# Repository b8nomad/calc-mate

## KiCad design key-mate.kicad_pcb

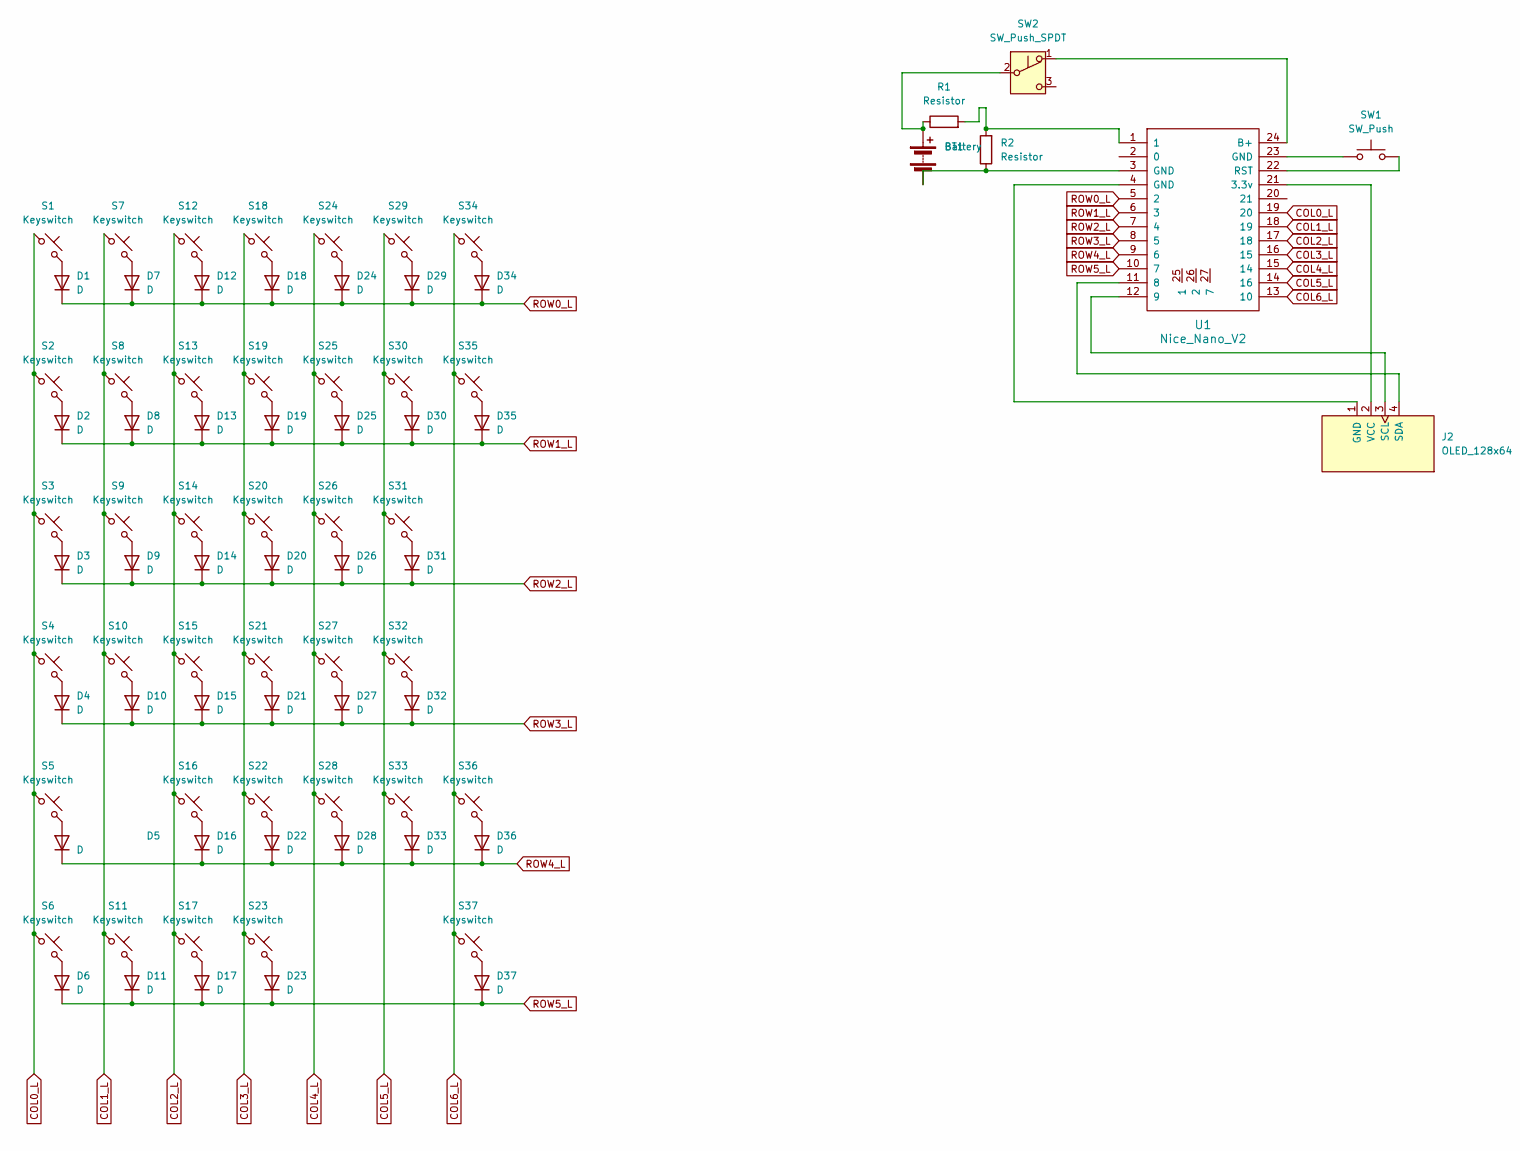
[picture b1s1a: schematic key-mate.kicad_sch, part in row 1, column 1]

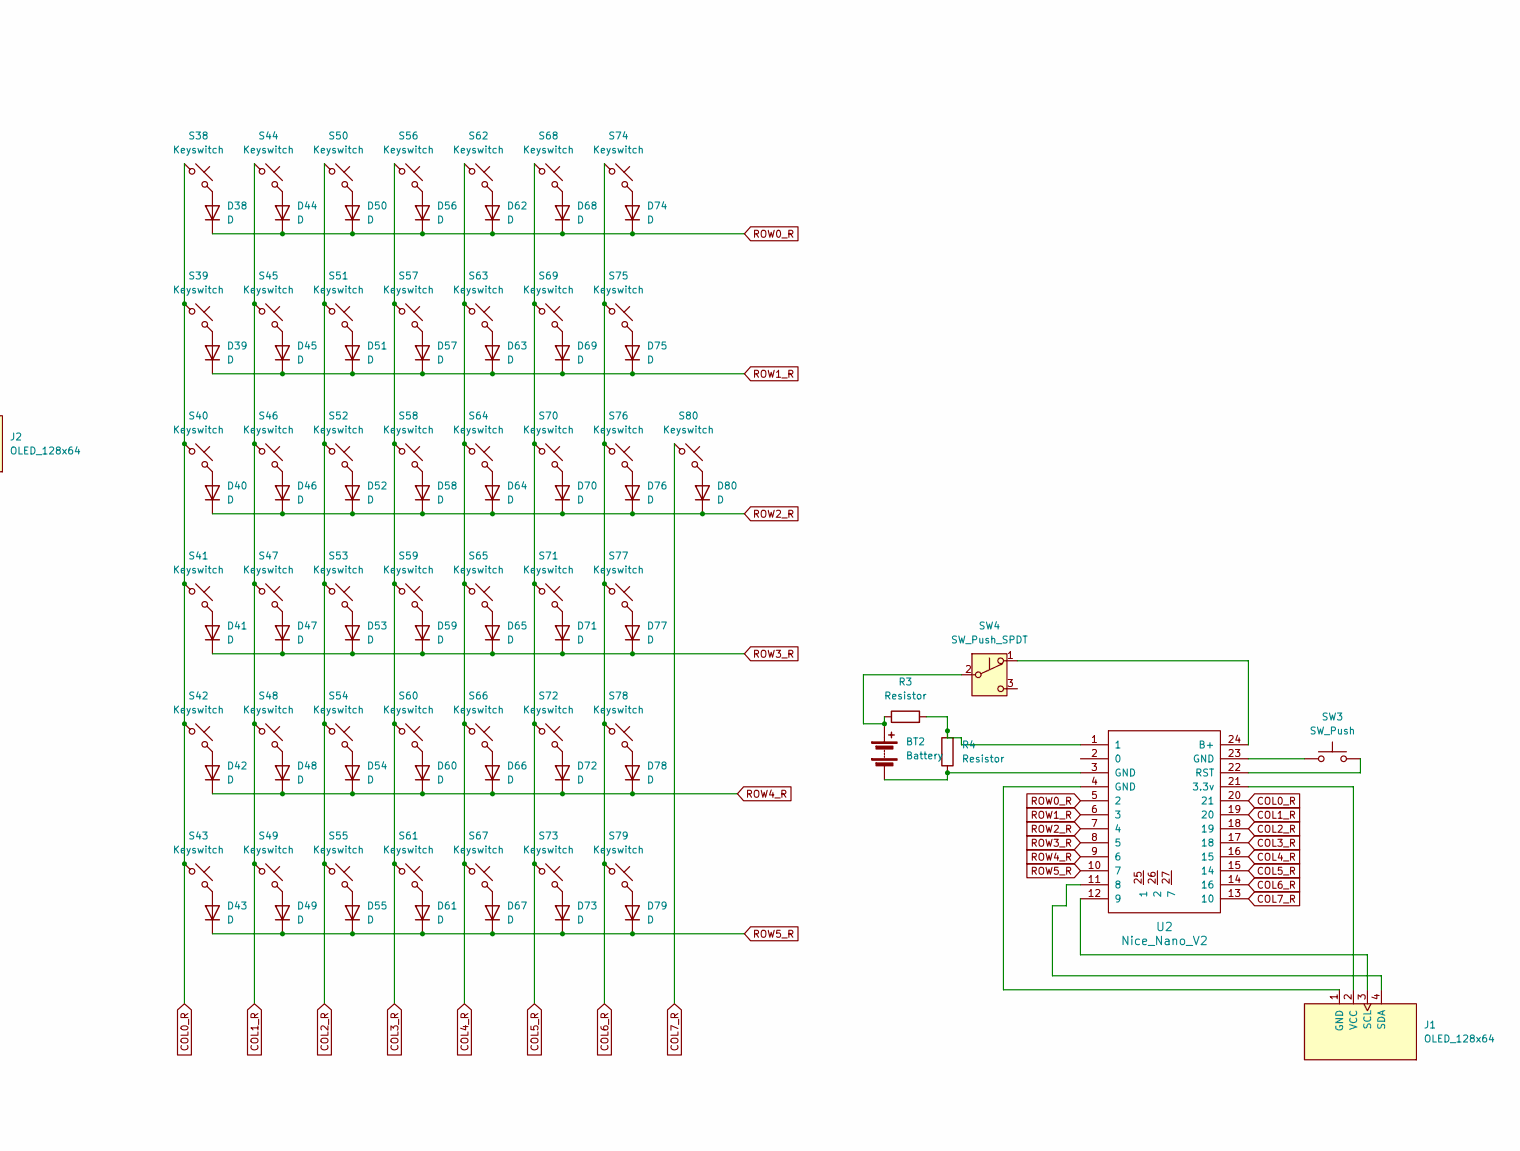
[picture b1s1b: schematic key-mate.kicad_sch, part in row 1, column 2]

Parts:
BT1, BT2: Battery
D1, D2, D3, D4, D5, D6, D7, D8, D9, D10, D11, D12, D13, D14, D15, D16, D17, D18, D19, D20, D21, D22, D23, D24, D25, D26, D27, D28, D29, D30, D31, D32, D33, D34, D35, D36, D37, D38, D39, D40, D41, D42, D43, D44, D45, D46, D47, D48, D49, D50, D51, D52, D53, D54, D55, D56, D57, D58, D59, D60, D61, D62, D63, D64, D65, D66, D67, D68, D69, D70, D71, D72, D73, D74, D75, D76, D77, D78, D79, D80: D; Diode_SOD-123
J1, J2: OLED_128x64
R1, R3: Resistor; Resistor_0402
R2, R4: Resistor; Resistor_0805
S1, S3, S75: Keyswitch; Hotswap_MX_1.50u
S2, S6, S7, S8, S9, S10, S11, S12, S13, S14, S15, S16, S17, S18, S19, S20, S21, S22, S23, S24, S25, S26, S27, S28, S29, S30, S31, S32, S33, S34, S35, S36, S38, S39, S40, S41, S42, S44, S45, S46, S47, S48, S49, S50, S51, S52, S53, S54, S55, S56, S57, S58, S59, S60, S61, S62, S63, S64, S65, S66, S67, S68, S69, S70, S71, S73, S74, S76, S78, S79, S80: Keyswitch; Hotswap_MX_1.00u
S4, S77: Keyswitch; Hotswap_MX_1.75u
S5, S72: Keyswitch; Hotswap_MX_2.25u
S37: Keyswitch; Hotswap_MX_3.00u
S43: Keyswitch; Hotswap_MX_4.00u
SW1, SW3: SW_Push; Button_MJTP1243
SW2, SW4: SW_Push_SPDT; Switch_SSAL220100
U1, U2: Nice_Nano_V2

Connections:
COL0_L: S1.1, S2.1, S3.1, S4.1, S5.1, S6.1, U1.19 (20)
COL0_R: S38.1, S39.1, S40.1, S41.1, S42.1, S43.1, U2.20 (21)
COL1_L: S7.1, S8.1, S9.1, S10.1, S11.1, U1.18 (19)
COL1_R: S44.1, S45.1, S46.1, S47.1, S48.1, S49.1, U2.19 (20)
COL2_L: S12.1, S13.1, S14.1, S15.1, S16.1, S17.1, U1.17 (18)
COL2_R: S50.1, S51.1, S52.1, S53.1, S54.1, S55.1, U2.18 (19)
COL3_L: S18.1, S19.1, S20.1, S21.1, S22.1, S23.1, U1.16 (15)
COL3_R: S56.1, S57.1, S58.1, S59.1, S60.1, S61.1, U2.17 (18)
COL4_L: S24.1, S25.1, S26.1, S27.1, S28.1, U1.15 (14)
COL4_R: S62.1, S63.1, S64.1, S65.1, S66.1, S67.1, U2.16 (15)
COL5_L: S29.1, S30.1, S31.1, S32.1, S33.1, U1.14 (16)
COL5_R: S68.1, S69.1, S70.1, S71.1, S72.1, S73.1, U2.15 (14)
COL6_L: S34.1, S35.1, S36.1, S37.1, U1.13 (10)
COL6_R: S74.1, S75.1, S76.1, S77.1, S78.1, S79.1, U2.14 (16)
COL7_R: S80.1, U2.13 (10)
unnamed: BT1.1 (+), R1.1, SW2.2 (B)
unnamed: BT1.2 (-), R2.1, U1.3 (GND)
unnamed: BT2.1 (+), R3.1, SW4.2 (B)
unnamed: BT2.2 (-), R4.1, U2.3 (GND)
unnamed: D1.2 (A), S1.2
unnamed: D2.2 (A), S2.2
unnamed: D3.2 (A), S3.2
unnamed: D4.2 (A), S4.2
unnamed: D5.2 (A), S5.2
unnamed: D6.2 (A), S6.2
unnamed: D7.2 (A), S7.2
unnamed: D8.2 (A), S8.2
unnamed: D9.2 (A), S9.2
unnamed: D10.2 (A), S10.2
unnamed: D11.2 (A), S11.2
unnamed: D12.2 (A), S12.2
unnamed: D13.2 (A), S13.2
unnamed: D14.2 (A), S14.2
unnamed: D15.2 (A), S15.2
unnamed: D16.2 (A), S16.2
unnamed: D17.2 (A), S17.2
unnamed: D18.2 (A), S18.2
unnamed: D19.2 (A), S19.2
unnamed: D20.2 (A), S20.2
unnamed: D21.2 (A), S21.2
unnamed: D22.2 (A), S22.2
unnamed: D23.2 (A), S23.2
unnamed: D24.2 (A), S24.2
unnamed: D25.2 (A), S25.2
unnamed: D26.2 (A), S26.2
unnamed: D27.2 (A), S27.2
unnamed: D28.2 (A), S28.2
unnamed: D29.2 (A), S29.2
unnamed: D30.2 (A), S30.2
unnamed: D31.2 (A), S31.2
unnamed: D32.2 (A), S32.2
unnamed: D33.2 (A), S33.2
unnamed: D34.2 (A), S34.2
unnamed: D35.2 (A), S35.2
unnamed: D36.2 (A), S36.2
unnamed: D37.2 (A), S37.2
unnamed: D38.2 (A), S38.2
unnamed: D39.2 (A), S39.2
unnamed: D40.2 (A), S40.2
unnamed: D41.2 (A), S41.2
unnamed: D42.2 (A), S42.2
unnamed: D43.2 (A), S43.2
unnamed: D44.2 (A), S44.2
unnamed: D45.2 (A), S45.2
unnamed: D46.2 (A), S46.2
unnamed: D47.2 (A), S47.2
unnamed: D48.2 (A), S48.2
unnamed: D49.2 (A), S49.2
unnamed: D50.2 (A), S50.2
unnamed: D51.2 (A), S51.2
unnamed: D52.2 (A), S52.2
unnamed: D53.2 (A), S53.2
unnamed: D54.2 (A), S54.2
unnamed: D55.2 (A), S55.2
unnamed: D56.2 (A), S56.2
unnamed: D57.2 (A), S57.2
unnamed: D58.2 (A), S58.2
unnamed: D59.2 (A), S59.2
unnamed: D60.2 (A), S60.2
unnamed: D61.2 (A), S61.2
unnamed: D62.2 (A), S62.2
unnamed: D63.2 (A), S63.2
unnamed: D64.2 (A), S64.2
unnamed: D65.2 (A), S65.2
unnamed: D66.2 (A), S66.2
unnamed: D67.2 (A), S67.2
unnamed: D68.2 (A), S68.2
unnamed: D69.2 (A), S69.2
unnamed: D70.2 (A), S70.2
unnamed: D71.2 (A), S71.2
unnamed: D72.2 (A), S72.2
unnamed: D73.2 (A), S73.2
unnamed: D74.2 (A), S74.2
unnamed: D75.2 (A), S75.2
unnamed: D76.2 (A), S76.2
unnamed: D77.2 (A), S77.2
unnamed: D78.2 (A), S78.2
unnamed: D79.2 (A), S79.2
unnamed: D80.2 (A), S80.2
unnamed: J1.1 (GND), U2.4 (GND)
unnamed: J1.3 (SCL), U2.12 (9)
unnamed: J1.4 (SDA), U2.11 (8)
unnamed: J1.2 (VCC), U2.21 (3.3v)
unnamed: J2.1 (GND), U1.4 (GND)
unnamed: J2.3 (SCL), U1.12 (9)
unnamed: J2.4 (SDA), U1.11 (8)
unnamed: J2.2 (VCC), U1.21 (3.3v)
unnamed: R1.2, R2.2, U1.1
unnamed: R3.2, R4.2, U2.1
unnamed: SW1.1, U1.23 (GND)
unnamed: SW2.1 (A), U1.24 (B+)
unnamed: SW3.1, U2.23 (GND)
unnamed: SW4.1 (A), U2.24 (B+)
unnamed: SW1.2, U1.22 (RST)
unnamed: SW3.2, U2.22 (RST)
ROW0_L: D1.1 (K), D7.1 (K), D12.1 (K), D18.1 (K), D24.1 (K), D29.1 (K), D34.1 (K), U1.5 (2)
ROW0_R: D38.1 (K), D44.1 (K), D50.1 (K), D56.1 (K), D62.1 (K), D68.1 (K), D74.1 (K), U2.5 (2)
ROW1_L: D2.1 (K), D8.1 (K), D13.1 (K), D19.1 (K), D25.1 (K), D30.1 (K), D35.1 (K), U1.6 (3)
ROW1_R: D39.1 (K), D45.1 (K), D51.1 (K), D57.1 (K), D63.1 (K), D69.1 (K), D75.1 (K), U2.6 (3)
ROW2_L: D3.1 (K), D9.1 (K), D14.1 (K), D20.1 (K), D26.1 (K), D31.1 (K), U1.7 (4)
ROW2_R: D40.1 (K), D46.1 (K), D52.1 (K), D58.1 (K), D64.1 (K), D70.1 (K), D76.1 (K), D80.1 (K), U2.7 (4)
ROW3_L: D4.1 (K), D10.1 (K), D15.1 (K), D21.1 (K), D27.1 (K), D32.1 (K), U1.8 (5)
ROW3_R: D41.1 (K), D47.1 (K), D53.1 (K), D59.1 (K), D65.1 (K), D71.1 (K), D77.1 (K), U2.8 (5)
ROW4_L: D5.1 (K), D16.1 (K), D22.1 (K), D28.1 (K), D33.1 (K), D36.1 (K), U1.9 (6)
ROW4_R: D42.1 (K), D48.1 (K), D54.1 (K), D60.1 (K), D66.1 (K), D72.1 (K), D78.1 (K), U2.9 (6)
ROW5_L: D6.1 (K), D11.1 (K), D17.1 (K), D23.1 (K), D37.1 (K), U1.10 (7)
ROW5_R: D43.1 (K), D49.1 (K), D55.1 (K), D61.1 (K), D67.1 (K), D73.1 (K), D79.1 (K), U2.10 (7)

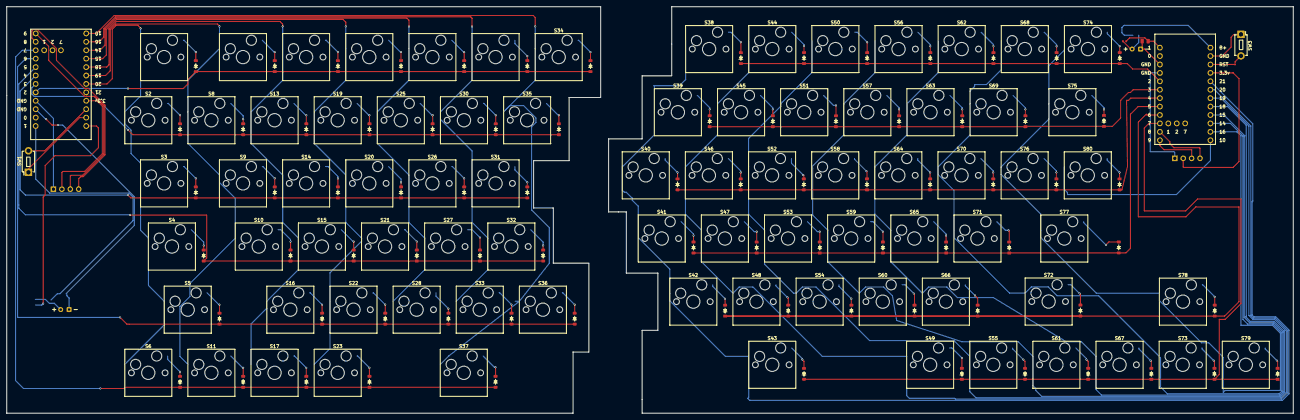
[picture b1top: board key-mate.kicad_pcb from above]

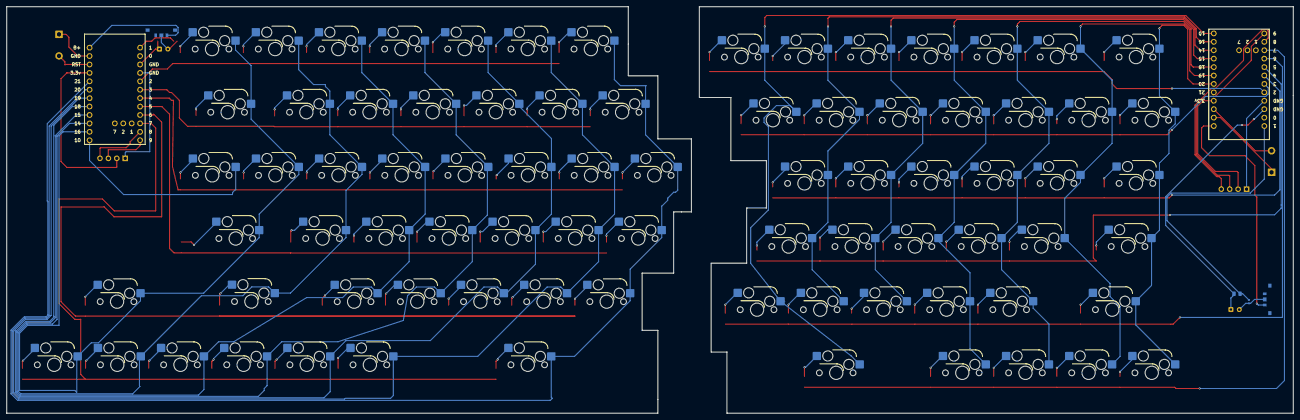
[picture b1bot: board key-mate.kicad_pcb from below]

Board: 2 copper layers, 388.1 x 122.6 mm, 174 parts (5 on the bottom side), 127 nets.

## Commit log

2025-10-25 ~ pcb files
